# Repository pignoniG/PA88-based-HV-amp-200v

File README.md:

# PA88-based-HV-amp-200v
PA88 based HV amp 200v

This is (hopefully) a precision amplifier.
It is setup for 20x amplification and maximum output a bit over +-200v
Maximum output at higher frequency (> 20kHz) is limited. I will publish test data as I complete the project.

The power supply section is based on a design by https://www.changpuak.ch/electronics/VB408.php

It uses 2 A41-25-230L Transformers, these transformers can be configured both for 115V and 220V input. These are not 1:1 transformers, the 220V output is at rated current, with lower current voltage can be quite higher, I decided to wire them in reverse compared to the marking to have slightly lower voltage into the power supply, and avoid stressing the 400v capacitors.

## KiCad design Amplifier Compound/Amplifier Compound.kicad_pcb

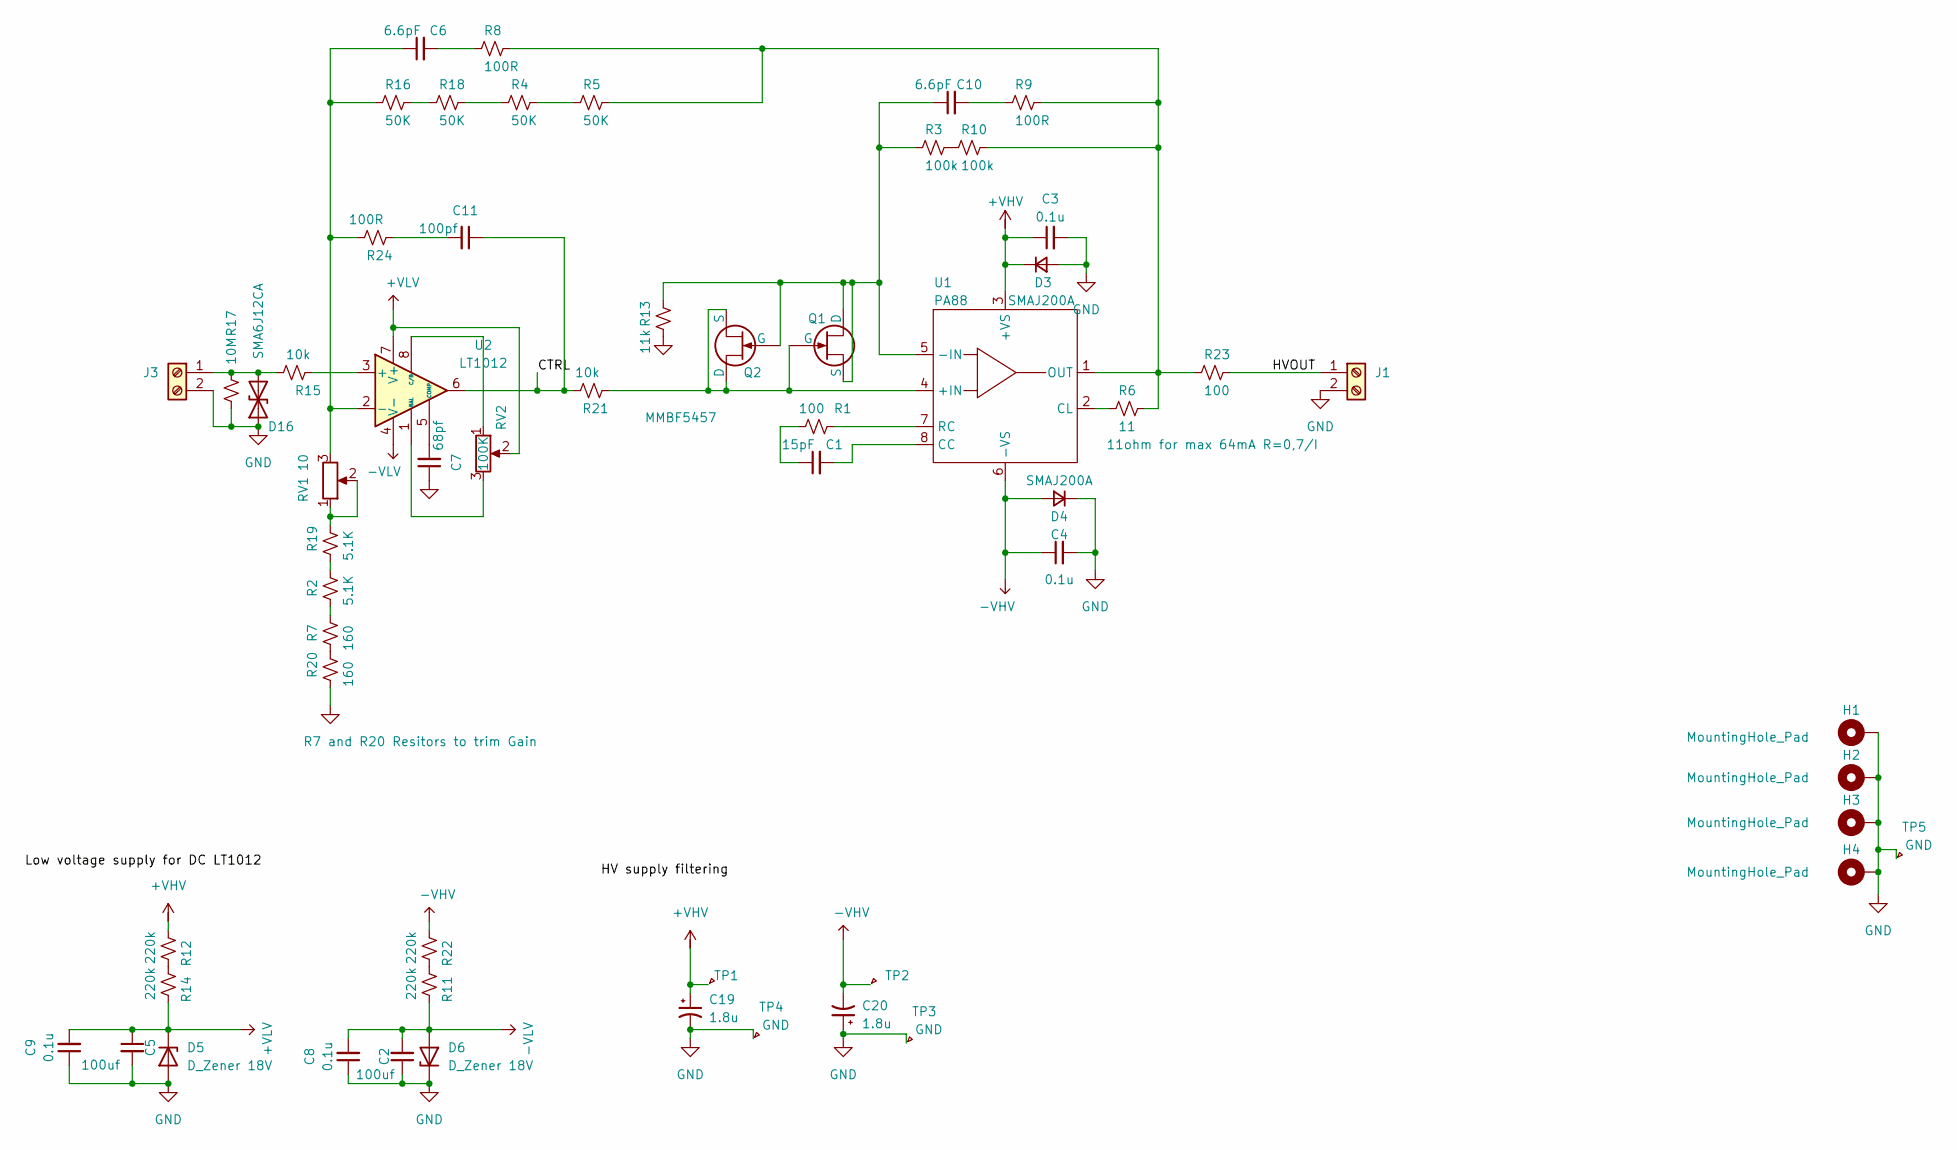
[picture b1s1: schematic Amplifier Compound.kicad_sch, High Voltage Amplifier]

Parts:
C1: 15pF; C_1206_3216Metric_Pad1.33x1.80mm_HandSolder; Voltage 50V; Part Description CAP CER 15PF 50V C0G/NP0 1206
C2: 100uf; CP_Elec_6.3x7.7; Voltage 25v
C3, C4, C8, C9: 0.1u; C_1206_3216Metric_Pad1.33x1.80mm_HandSolder; Voltage 450V; Part Description CAP CER 0.1UF 450V X7T 1206
C5: 100uf; CP_Elec_6.3x7.7; Voltage 24v
C6, C10: 6.6pF; C_1206_3216Metric_Pad1.33x1.80mm_HandSolder; Voltage 450V; Part Description CAP CER 15PF 450V C0G/NP0 1206
C7: 68pf; C_1206_3216Metric_Pad1.33x1.80mm_HandSolder; Voltage 50V; Part Description CAP CER 15PF 50V C0G/NP0 1206
C11: 100pf; C_1206_3216Metric_Pad1.33x1.80mm_HandSolder; Voltage 50V; Part Description CAP CER 15PF 50V C0G/NP0 1206
C19, C20: 1.8u; C_Elec_8x10.2; Voltage 400V; Mfg Part Number UUB2G1R8MNL1GS
D3, D4: SMAJ200A; D_SMA_Handsoldering; Mfg Part Number SMAJ200A-TP
D5, D6: D_Zener 18V; D_A-405_P10.16mm_Horizontal
D16: SMA6J12CA; D_SMA_Handsoldering; Mfg Part Number SMA6J5.0CA
H1, H2, H3, H4: MountingHole_Pad; MountingHole_3.2mm_M3_DIN965_Pad_TopBottom
J1, J3: Screw_Terminal_01x02; Molex_KK-396_A-41791-0002_1x02_P3.96mm_Vertical; Mfg Part Number 31101102
Q1, Q2: MMBF5457; SOT-23-3
R1: 100; R_1206_3216Metric_Pad1.30x1.75mm_HandSolder; Part Description RES SMD 100 OHM 1% 1/4W 1206
R2, R19: 5.1K; R_1206_3216Metric_Pad1.30x1.75mm_HandSolder; Part Description RES SMD 16.9K OHM 1% 1/4W 1206
R3, R10: 100k; R_1206_3216Metric_Pad1.30x1.75mm_HandSolder
R4, R5, R16, R18: 50K; R_1206_3216Metric_Pad1.30x1.75mm_HandSolder
R6: 11; R_1206_3216Metric_Pad1.30x1.75mm_HandSolder; Part Description RES 150 OHM 1% 1/2W 1206
R7, R20: 160; R_1206_3216Metric_Pad1.30x1.75mm_HandSolder; Part Description RES SMD 16.9K OHM 1% 1/4W 1206
R8, R9: 100R; R_1206_3216Metric_Pad1.30x1.75mm_HandSolder
R11, R12, R14, R22: 220k; R_Axial_DIN0411_L9.9mm_D3.6mm_P5.08mm_Vertical; Part Description RES SMD 16.9K OHM 1% 1/4W 1206
R13: 11k; R_1206_3216Metric_Pad1.30x1.75mm_HandSolder
R15, R21: 10k; R_1206_3216Metric_Pad1.30x1.75mm_HandSolder; Part Description RES SMD 100 OHM 1% 1/4W 1206
R17: 10M; R_1206_3216Metric_Pad1.30x1.75mm_HandSolder; Part Description RES SMD 100 OHM 1% 1/4W 1206
R23: 100; R_1206_3216Metric_Pad1.30x1.75mm_HandSolder; Part Description RES 150 OHM 1% 1/2W 1206
R24: 100R; R_1206_3216Metric_Pad1.30x1.75mm_HandSolder; Part Description RES SMD 100 OHM 1% 1/4W 1206
RV1: 10; Potentiometer_Bourns_3005_Horizontal; Mfg Part Number CT20EP503
RV2: 100K; Potentiometer_Bourns_3005_Horizontal; Mfg Part Number CT20EP503
TP1: +VHV; TestPoint_THTPad_2.5x2.5mm_Drill1.2mm
TP2: -VHV; TestPoint_THTPad_2.5x2.5mm_Drill1.2mm
TP3, TP4, TP5: GND; TestPoint_THTPad_2.5x2.5mm_Drill1.2mm
U1: PA88; TO-3-8; Mfg Part Number PA88
U2: LT1012; DIP-8_W7.62mm_LongPads

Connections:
+VHV: C3.1, C19.1, D3.1 (K), R12.2, TP1.1, U1.3 (+VS)
+VLV: C5.1, C9.2, D5.1 (K), R14.1, RV2.2, U2.7 (V+)
-VHV: C4.1, C20.2, D4.2 (A), R22.2, TP2.1, U1.6 (-VS)
-VLV: C2.2, C8.2, D6.2 (A), R11.1, U2.4 (V-)
/CTRL: C11.1, R21.1, U2.6
/HVOUT: J1.1, R23.1
GND: C2.1, C3.2, C4.2, C5.2, C7.1, C8.1, C9.1, C19.2, C20.1, D3.2 (A), D4.1 (K), D5.2 (A), D6.1 (K), D16.1 (A1), H1.1, H2.1, H3.1, H4.1, J1.2, J3.2, R13.2, R17.1, R20.2, TP3.1, TP4.1, TP5.1
unnamed: C1.1, R1.1
unnamed: C6.2, R8.2
unnamed: C10.2, R9.2
unnamed: C11.2, R24.2
unnamed: D16.2 (A2), J3.1, R15.2, R17.2
unnamed: C10.1, Q1.1 (D), Q1.2 (S), Q2.3 (G), R3.2, R13.1, U1.5 (-IN)
unnamed: Q1.3 (G), Q2.1 (D), Q2.2 (S), R21.2, U1.4 (+IN)
unnamed: R2.2, R7.1
unnamed: R4.1, R5.2
unnamed: R3.1, R10.2
unnamed: R11.2, R22.1
unnamed: R12.1, R14.2
unnamed: R16.1, R18.2
unnamed: R4.2, R18.1
unnamed: R19.1, RV1.1, RV1.2
unnamed: R2.1, R19.2
unnamed: R7.2, R20.1
unnamed: C1.2, U1.8 (CC)
unnamed: R6.2, U1.2 (CL)
unnamed: R5.1, R6.1, R8.1, R9.1, R10.1, R23.2, U1.1 (OUT)
unnamed: R1.2, U1.7 (RC)
unnamed: R15.1, U2.3 (+)
unnamed: C6.1, R16.2, R24.1, RV1.3, U2.2 (-)
unnamed: RV2.3, U2.1 (BAL)
unnamed: C7.2, U2.5 (COMP)
unnamed: RV2.1, U2.8 (C/B)

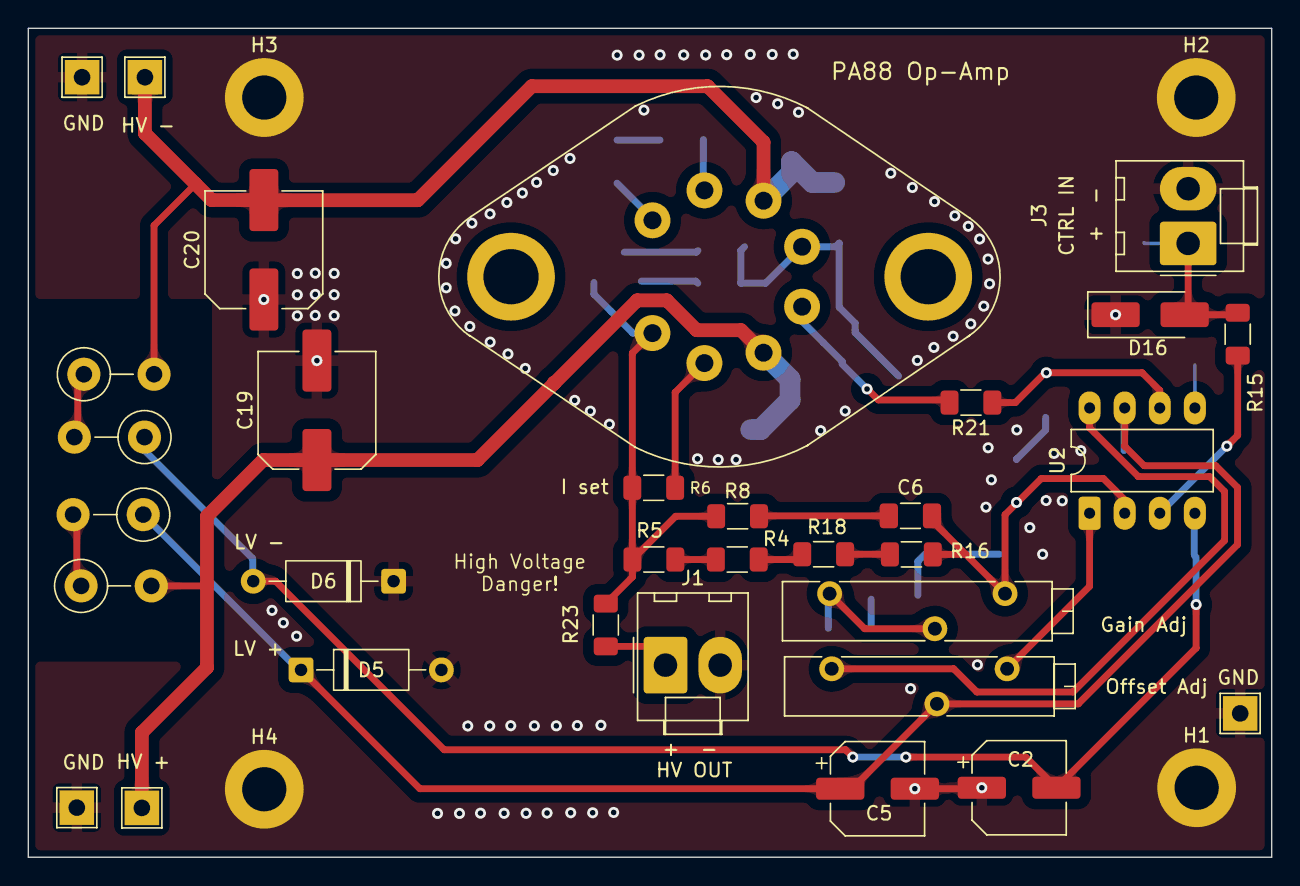
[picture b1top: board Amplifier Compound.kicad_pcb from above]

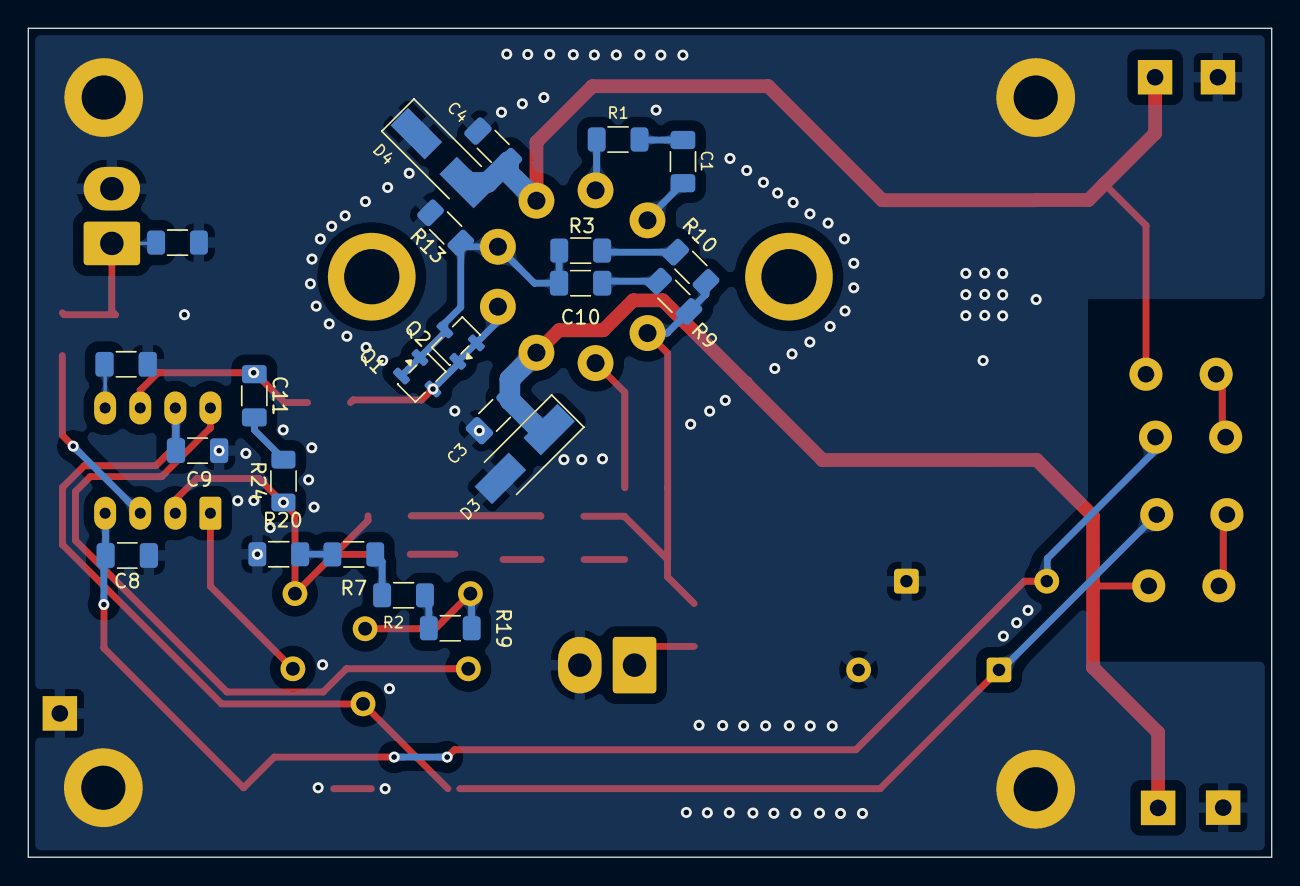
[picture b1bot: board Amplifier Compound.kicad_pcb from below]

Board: 2 copper layers, 90.0 x 60.0 mm, 59 parts (23 on the bottom side), 33 nets.

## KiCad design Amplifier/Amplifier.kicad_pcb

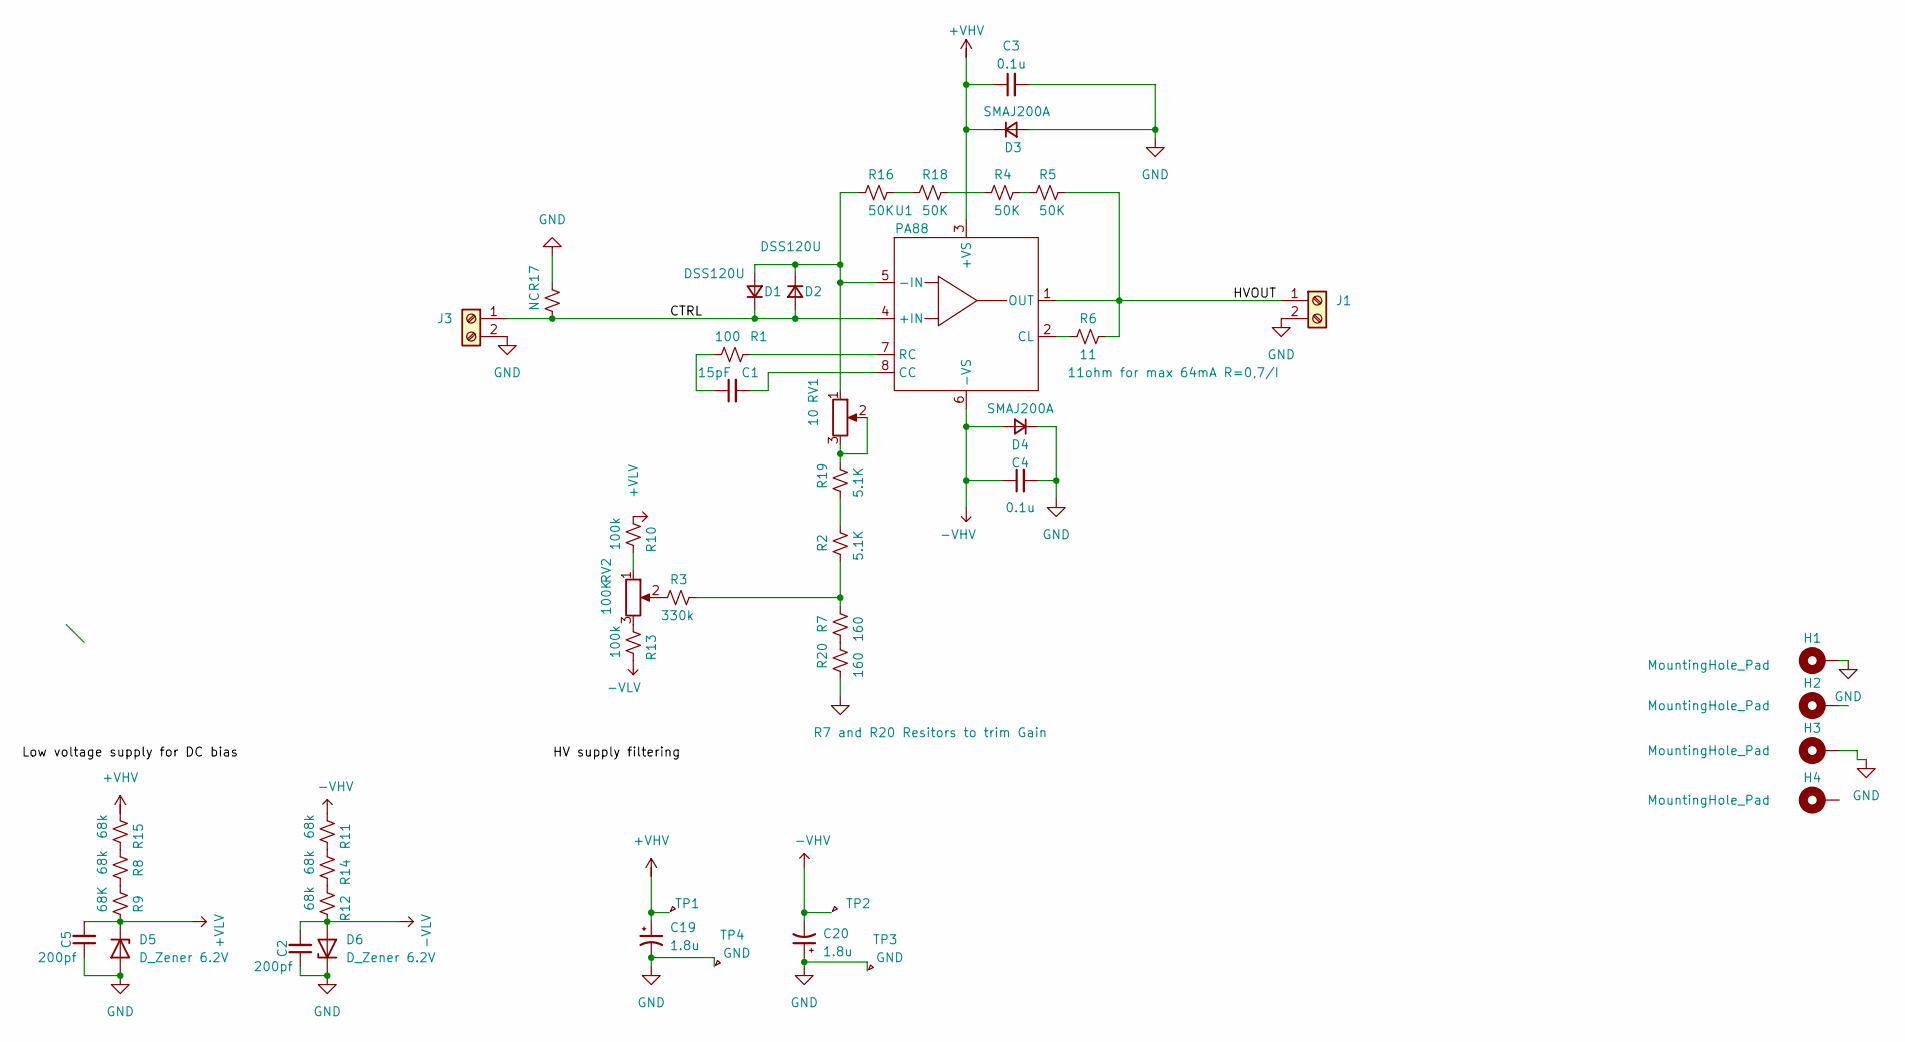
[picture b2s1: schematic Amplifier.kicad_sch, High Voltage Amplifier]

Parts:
C1: 15pF; C_1206_3216Metric_Pad1.33x1.80mm_HandSolder; Voltage 50V; Part Description CAP CER 15PF 50V C0G/NP0 1206
C2, C5: 200pf; C_1206_3216Metric_Pad1.33x1.80mm_HandSolder; Voltage 450V; Part Description CAP CER 0.1UF 450V X7T 1206
C3, C4: 0.1u; C_1206_3216Metric_Pad1.33x1.80mm_HandSolder; Voltage 450V; Part Description CAP CER 0.1UF 450V X7T 1206
C19, C20: 1.8u; C_Elec_8x10.2; Voltage 400V; Mfg Part Number UUB2G1R8MNL1GS
D1, D2: DSS120U; D_SOD-123F; Mfg Part Number DSS120U
D3, D4: SMAJ200A; D_SMA_Handsoldering; Mfg Part Number SMAJ200A-TP
D5, D6: D_Zener 6.2V; D_MiniMELF
H1, H2, H3, H4: MountingHole_Pad; MountingHole_3.2mm_M3_DIN965_Pad
J1, J3: Screw_Terminal_01x02; PhoenixContact_MCV_1,5_2-G-3.5_1x02_P3.50mm_Vertical; Mfg Part Number 31101102
R1: 100; R_1206_3216Metric_Pad1.30x1.75mm_HandSolder; Part Description RES SMD 100 OHM 1% 1/4W 1206
R2, R19: 5.1K; R_1206_3216Metric_Pad1.30x1.75mm_HandSolder; Part Description RES SMD 16.9K OHM 1% 1/4W 1206
R3: 330k; R_1206_3216Metric_Pad1.30x1.75mm_HandSolder; Part Description RES SMD 16.9K OHM 1% 1/4W 1206
R4, R5, R16, R18: 50K; R_1206_3216Metric_Pad1.30x1.75mm_HandSolder
R6: 11; R_1206_3216Metric_Pad1.30x1.75mm_HandSolder; Part Description RES 150 OHM 1% 1/2W 1206
R7, R20: 160; R_1206_3216Metric_Pad1.30x1.75mm_HandSolder; Part Description RES SMD 16.9K OHM 1% 1/4W 1206
R8, R11, R12, R14, R15: 68k; R_1206_3216Metric_Pad1.30x1.75mm_HandSolder; Part Description RES SMD 16.9K OHM 1% 1/4W 1206
R9: 68K; R_1206_3216Metric_Pad1.30x1.75mm_HandSolder; Part Description RES SMD 16.9K OHM 1% 1/4W 1206
R10, R13: 100k; R_1206_3216Metric_Pad1.30x1.75mm_HandSolder; Part Description RES SMD 16.9K OHM 1% 1/4W 1206
R17: NC; R_1206_3216Metric_Pad1.30x1.75mm_HandSolder; Part Description RES SMD 100 OHM 1% 1/4W 1206
RV1: 10; Potentiometer_Bourns_3005_Horizontal; Mfg Part Number CT20EP503
RV2: 100K; Potentiometer_Bourns_3005_Horizontal; Mfg Part Number CT20EP503
TP1: +VHV; TestPoint_THTPad_2.5x2.5mm_Drill1.2mm
TP2: -VHV; TestPoint_THTPad_2.5x2.5mm_Drill1.2mm
TP3, TP4: GND; TestPoint_THTPad_2.5x2.5mm_Drill1.2mm
U1: PA88; TO-3-8; Mfg Part Number PA88

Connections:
+VHV: C3.1, C19.1, D3.1 (K), R15.2, TP1.1, U1.3 (+VS)
+VLV: C5.2, D5.1 (K), R9.1, R10.2
-VHV: C4.1, C20.2, D4.2 (A), R11.2, TP2.1, U1.6 (-VS)
-VLV: C2.2, D6.2 (A), R12.1, R13.1
/CTRL: D1.1 (K), D2.2 (A), J3.1, R17.1, U1.4 (+IN)
/HVOUT: J1.1, R5.1, R6.1, U1.1 (OUT)
GND: C2.1, C3.2, C4.2, C5.1, C19.2, C20.1, D3.2 (A), D4.1 (K), D5.2 (A), D6.1 (K), H1.1, H3.1, J1.2, J3.2, R17.2, R20.2, TP3.1, TP4.1
unnamed: C1.1, R1.1
unnamed: D1.2 (A), D2.1 (K), R16.2, RV1.1, U1.5 (-IN)
unnamed: R2.2, R3.1, R7.1
unnamed: R3.2, RV2.2
unnamed: R4.1, R5.2
unnamed: R8.1, R9.2
unnamed: R10.1, RV2.1
unnamed: R11.1, R14.2
unnamed: R12.2, R14.1
unnamed: R13.2, RV2.3
unnamed: R8.2, R15.1
unnamed: R16.1, R18.2
unnamed: R4.2, R18.1
unnamed: R19.1, RV1.2, RV1.3
unnamed: R2.1, R19.2
unnamed: R7.2, R20.1
unnamed: C1.2, U1.8 (CC)
unnamed: R6.2, U1.2 (CL)
unnamed: R1.2, U1.7 (RC)

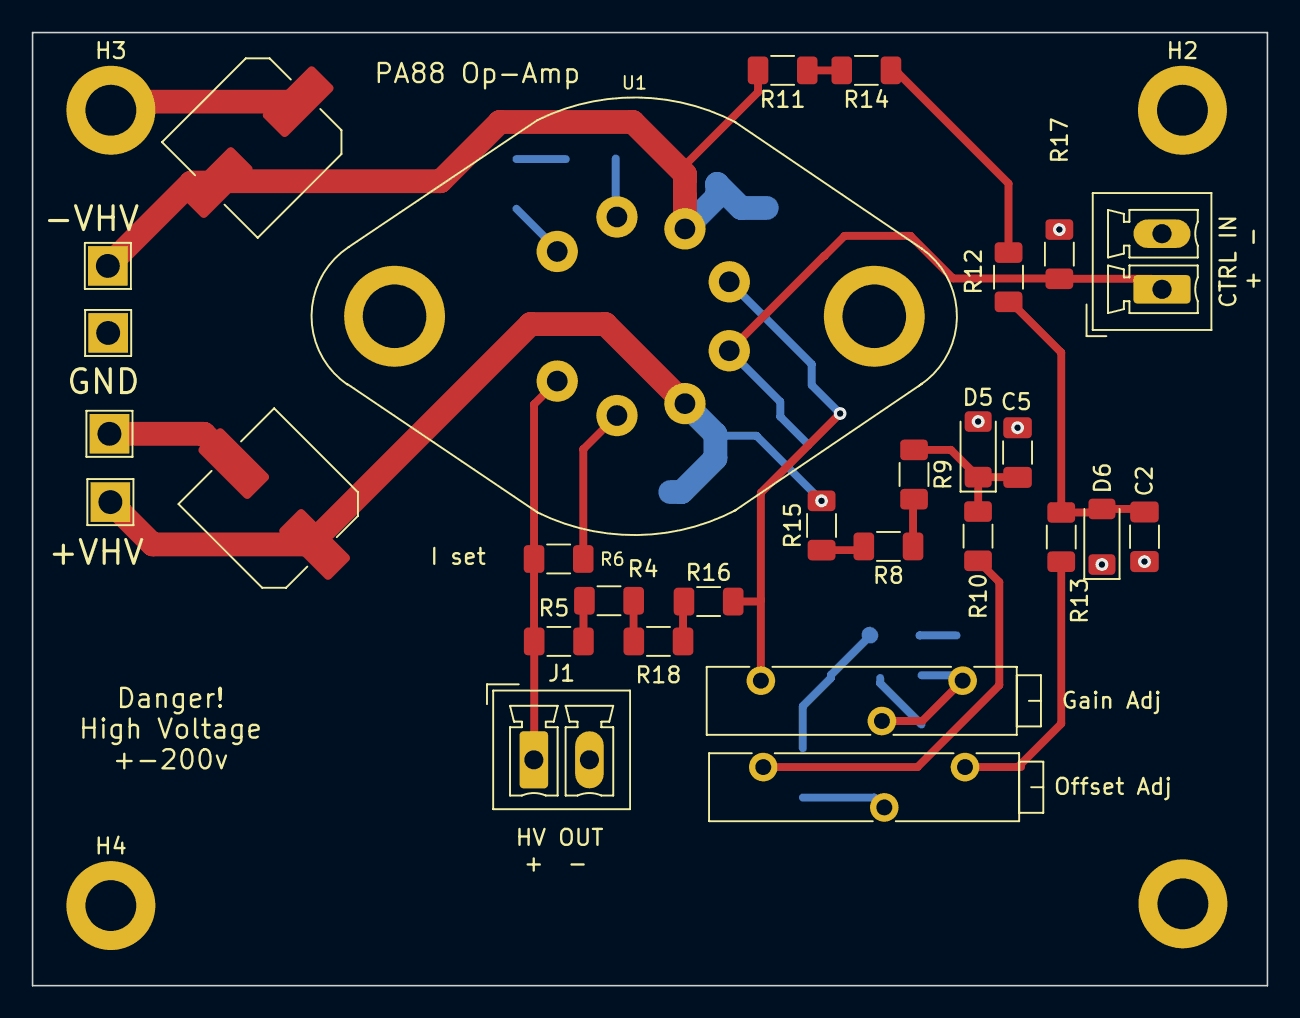
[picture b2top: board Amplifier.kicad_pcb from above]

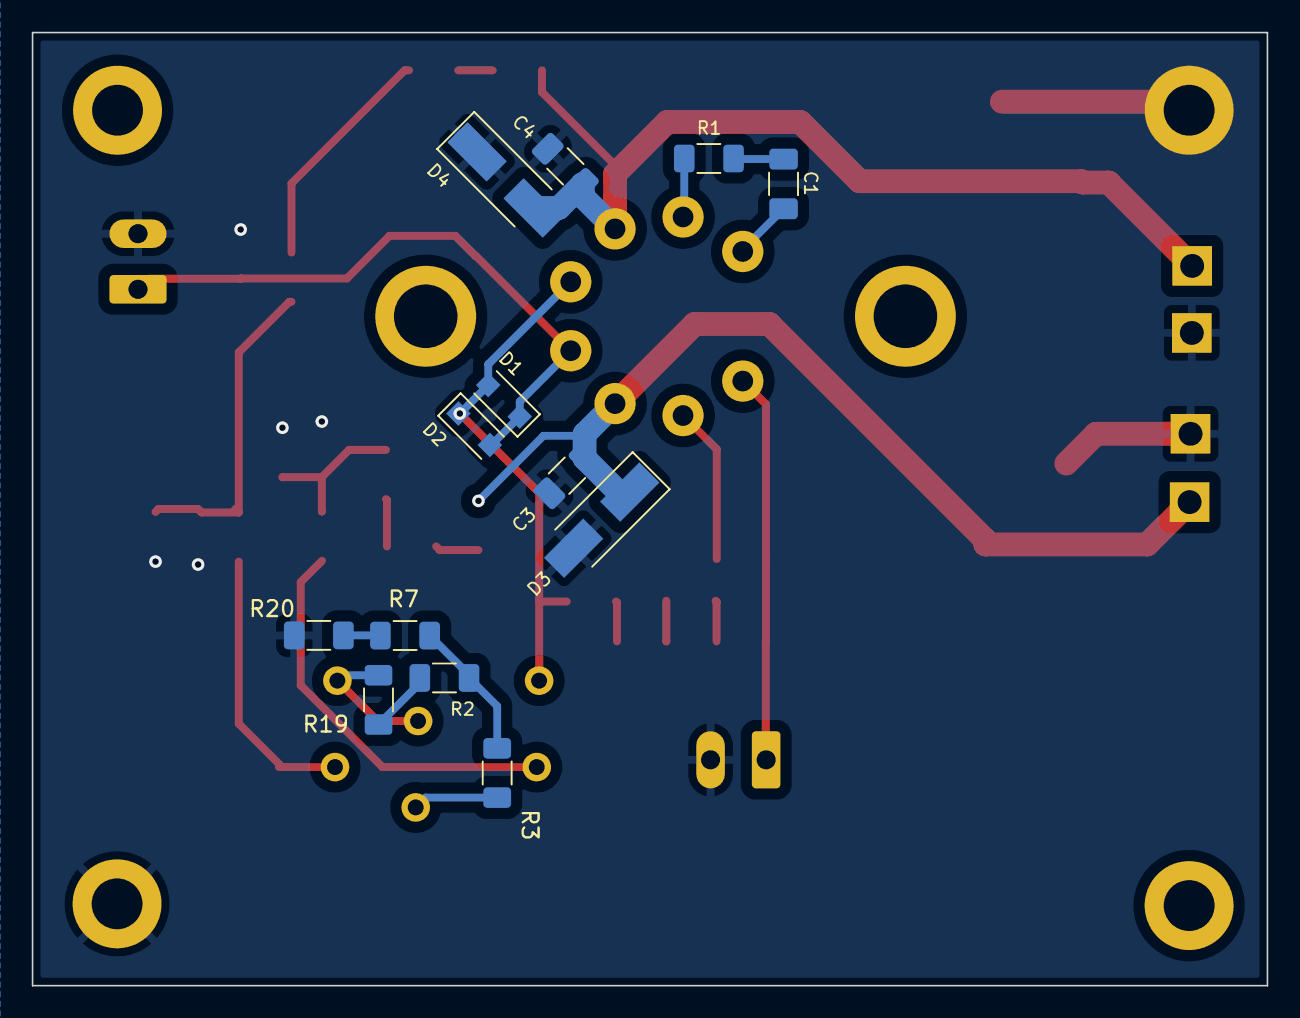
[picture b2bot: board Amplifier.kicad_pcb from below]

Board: 2 copper layers, 77.7 x 60.0 mm, 46 parts (13 on the bottom side), 26 nets.

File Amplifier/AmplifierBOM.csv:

Id;Designator;Footprint;Quantity;Designation;Supplier and ref;;
;;;;;;;
2;C2,C5;C_1206_3216Metric_Pad1.33x1.80mm_HandSolder;2;200pf;C1206C201J5GACTU;;
3;R13,R10;R_1206_3216Metric_Pad1.30x1.75mm_HandSolder;2;100k;;;
4;J1,J3;Molex_KK-396_A-41791-0002_1x02_P3.96mm_Vertical;2;;26-60-4020;;
;;;;;;;
6;R15,R8,R12,R14,R11;R_1206_3216Metric_Pad1.30x1.75mm_HandSolder;5;68k;;;
7;R6;R_1206_3216Metric_Pad1.30x1.75mm_HandSolder;1;11;;;
8;RV1;Potentiometer_Bourns_3005_Horizontal;1;10;3006P-1-100LF;;
9;R9;R_1206_3216Metric_Pad1.30x1.75mm_HandSolder;1;68K;;;
10;D5,D6;D_MiniMELF;2;D_Zener 6.2V;TZMB6V2-GS08;;
11;R5,R4;R_1206_3216Metric_Pad1.30x1.75mm_HandSolder;2;49.9K;PLT1206Z5002AST5;;
;;;;;;;
13;Termination;R_1206_3216Metric_Pad1.30x1.75mm_HandSolder;1;NC;;;
14;RV2;Potentiometer_Bourns_3005_Horizontal;1;100K;3006P-1-104LF;;
;;;;;;;
16;U1;TO-3-8;1;PA88;;;
17;C19,C20;C_Elec_8x10.2;2;1.8u;UUB2G1R8MNL1GS;;
18;R3;R_1206_3216Metric_Pad1.30x1.75mm_HandSolder;1;10M;;;
19;D1,D2;D_SOD-123F;2;;DSS120U;;
20;D4,D3;D_SMA_Handsoldering;2;;SMAJ220A;;
21;R7,R1;R_1206_3216Metric_Pad1.30x1.75mm_HandSolder;2;160;;;
22;R2;R_1206_3216Metric_Pad1.30x1.75mm_HandSolder;1;5.1K;TNPU12065K10BZEN00;;
23;C3,C4;C_1206_3216Metric_Pad1.33x1.80mm_HandSolder;2;0.1u;C3216X7T2W104K160AE;;
;;;;;;;
25;C1;C_1206_3216Metric_Pad1.33x1.80mm_HandSolder;1;15pF;12067A150FAT2A;;

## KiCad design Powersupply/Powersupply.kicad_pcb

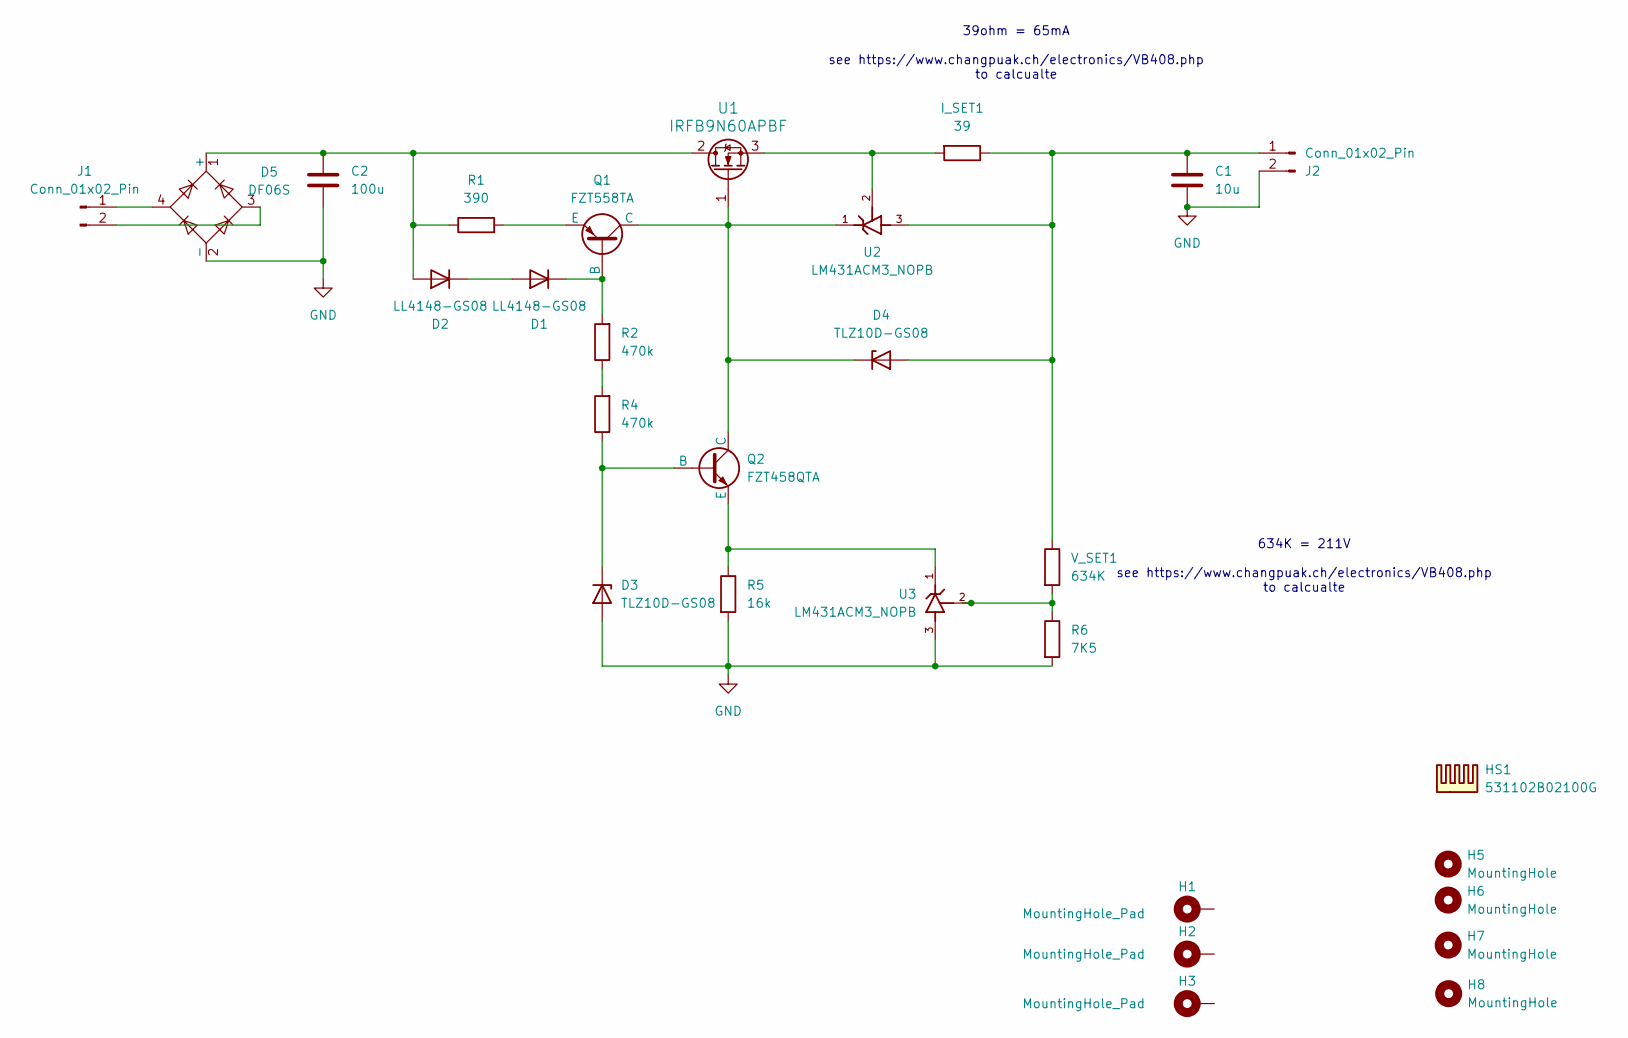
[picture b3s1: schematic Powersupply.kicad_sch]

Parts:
C1: 10u; CP_Radial_D12.5mm_P5.00mm
C2: 100u; CP_Radial_D30.0mm_P10.00mm_SnapIn
D1, D2: LL4148-GS08; D_MiniMELF
D3, D4: TLZ10D-GS08; D_MiniMELF
D5: DF06S; Diode_Bridge_OnSemi_SDIP-4L
H1, H2, H3: MountingHole_Pad; MountingHole_3.2mm_M3_DIN965_Pad
H5, H6, H7, H8: MountingHole; MountingHole_3mm
HS1: 531102B02100G; Heatsink_AAVID_Extruded_531102B02100G_34.9x12.7mm_H38.1mm
I_SET1: 39; C_0805_2012Metric_Pad1.18x1.45mm_HandSolder
J1, J2: Conn_01x02_Pin; Molex_KK-396_A-41791-0002_1x02_P3.96mm_Vertical
Q1: FZT558TA; SOT-223-3_TabPin2
Q2: FZT458QTA; SOT-223-3_TabPin2
R1: 390; C_0805_2012Metric_Pad1.18x1.45mm_HandSolder
R2, R4: 470k; C_0805_2012Metric_Pad1.18x1.45mm_HandSolder
R5: 16k; C_0805_2012Metric_Pad1.18x1.45mm_HandSolder
R6: 7K5; C_0805_2012Metric_Pad1.18x1.45mm_HandSolder
U1: IRFB9N60APBF; TO-220-3_Vertical
U2, U3: LM431ACM3_NOPB; SOT-23-3; PARTREV H
V_SET1: 634K; C_0805_2012Metric_Pad1.18x1.45mm_HandSolder

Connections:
GND: C1.2, C2.2, D3.2 (A), D5.2 (-), J2.2, R5.2, R6.2, U3.3
unnamed: D1.2 (A), D2.1 (K)
unnamed: D1.1 (K), Q1.1 (B), R2.2
unnamed: C2.1, D2.2 (A), D5.1 (+), R1.1, U1.2 (D)
unnamed: D3.1 (K), Q2.1 (B), R4.1
unnamed: C1.1, D4.2 (A), I_SET1.1, J2.1, U2.3, V_SET1.1
unnamed: D4.1 (K), Q1.2 (C), Q2.2 (C), U1.1 (G), U2.1
unnamed: D5.4, J1.1
unnamed: D5.3, J1.2
unnamed: Q1.3 (E), R1.2
unnamed: Q2.3 (E), R5.1, U3.1
unnamed: R2.1, R4.2
unnamed: R6.1, U3.2, V_SET1.2
unnamed: I_SET1.2, U1.3 (S), U2.2

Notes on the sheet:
634K = 211V see https://www.changpuak.ch/electronics/VB408.php to calcualte
39ohm = 65mA see https://www.changpuak.ch/electronics/VB408.php to calcualte

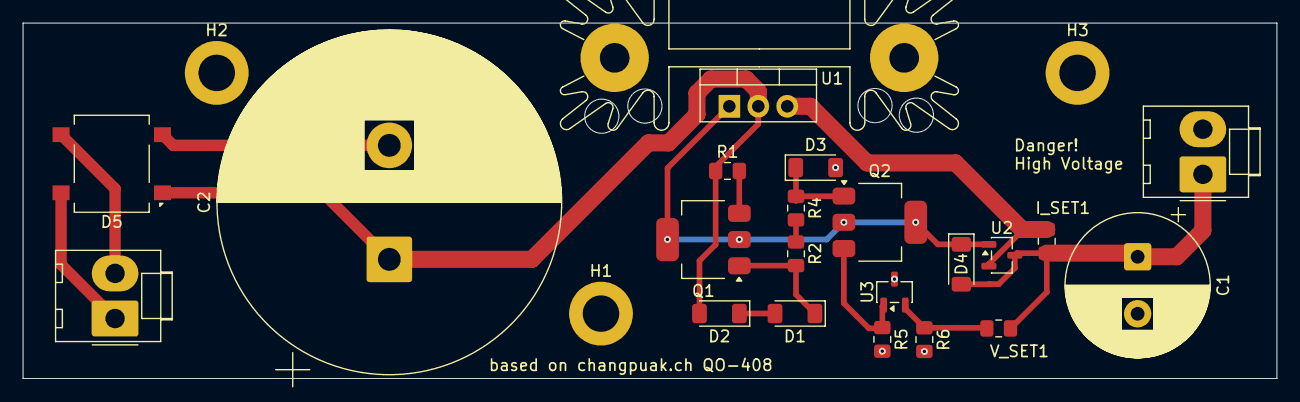
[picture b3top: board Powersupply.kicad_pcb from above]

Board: 2 copper layers, 110.0 x 31.2 mm, 29 parts (0 on the bottom side), 14 nets.

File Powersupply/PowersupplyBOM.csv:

Id;Designator;Footprint;Quantity;Designation;Supplier and ref;;
1;R6;C_0805_2012Metric_Pad1.18x1.45mm_HandSolder;1;7K5;;;
2;Q2;SOT-223-3_TabPin2;1;FZT458QTA;;;
;;;;;;;
4;C2;CP_Radial_D30.0mm_P10.00mm_SnapIn;1;LAS2G101MELZ25;;;
5;D3,D4;D_MiniMELF;2;TLZ10D-GS08;;;
6;R4,R2;C_0805_2012Metric_Pad1.18x1.45mm_HandSolder;2;470k;;;
7;I_SET1;C_0805_2012Metric_Pad1.18x1.45mm_HandSolder;1;39;;;
8;J2,J1;Molex_KK-396_A-41791-0002_1x02_P3.96mm_Vertical;2;26-60-4020;;;
9;D2,D1;D_MiniMELF;2;LL4148-GS08;;;
10;U1;TO-220-3_Vertical;1;IRFB9N60APBF;;;
11;V_SET1;C_0805_2012Metric_Pad1.18x1.45mm_HandSolder;1;634K;;;
12;C1;CP_Radial_D12.5mm_P5.00mm;1;"
EEU-EB2G100";;;
13;HS1;Heatsink_AAVID_Extruded_531102B02100G_34.9x12.7mm_H38.1mm;1;531102B02100G;;;
14;U2,U3;SOT-23-3;2;LM431ACM3_NOPB;;;
15;D5;Diode_Bridge_OnSemi_SDIP-4L;1;DF06S;;;
16;R1;C_0805_2012Metric_Pad1.18x1.45mm_HandSolder;1;390;;;
17;R5;C_0805_2012Metric_Pad1.18x1.45mm_HandSolder;1;16k;;;
18;Q1;SOT-223-3_TabPin2;1;FZT558TA;;;
;;;;;;;
;;Headers & Wire Housings HSG 2P W/LKG RAMP;4;09-50-3021;;;
;;Headers & Wire Housings KK 156 TERMINAL CRIMP;4;08-50-0015;;;

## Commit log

2025-11-24 init frontpanel
2025-11-24 init all
2025-11-24 update amplifier
2025-12-02 update feedback resistor to 200k
2025-12-04 compound
2025-12-21 update composite
2025-12-23 final components update
2025-12-23 clearance
2025-12-25 extra feedback
